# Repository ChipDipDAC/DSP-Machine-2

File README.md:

# DSP-Machine-2
Hi-Res Streamer - Preamp, for Raspberry Pi, XLR analog out<br>
<a class="link" href="https://www.chipdip.ru/catalog-show/for-you-projects?p.0=ChipDipDac"><strong>DSP Machine 2</strong></a> - стример, цифроаналоговый преобразователь ЦАП, аудиопроцессор, для микрокомпьютеров Raspberry Pi.<br />
Для построения стримера вы можете использовать любой микрокомпьютер Raspberry Pi. Микрокомпьютер устанавливается на 40-пиновый разъем аудио карты. В качестве ПО используйте любой плеер или ОС образ, которых записан на микроSD карточку для Raspberry Pi. Операционные системы автоматически определяют аудиокарту ChipDip DAC и настраивают вывод звука именно на неё. В некоторых плеерах может понадобится выбрать в качестве устройства вывода звука - ChipDip DAC.<br />
<br />
- Plug and Play не требует пайки<br />
- Совместим с Raspberry Pi<br />
- Официальная поддержка RaspberryPi OS / Volumio3 / rAudio1 / Album Player / OpenELEC / Manjaro OS / MoOde и другими.<br />
- Высококачественный ЦАП PCM5242 для наилучшего качества звука.<br />
- Разъемы аудиовыхода: 2 x XLR (левый и правый)<br />
- Встроенная EEPROM для автоматической настройки ОС (с защитой от записи).<br />
- Автоматическое переключение частот в соответствии с входными сигналами I2S.<br />
- Диапазон частот дискретизации и разрядности от 44,1кГц/16 бит до 192кГц/32 бит<br />
- Совместим с ПО PurePathStudio и ChipStudio для перестройки аудиопроцессора<br />
Задать вопросы можно на форуме в разделе <a class="link" href="https://forum.chipdip.ru/index.php#chipdip-dac.39">ChipDip DAC</a>
<p></p>

<p></p>

<h2>Что под крышкой *</h2>

<p></p>

<p></p>
* Микрокомпьютер Raspberry Pi в комплект не входит.

<h2>Сравнительная таблица</h2>

<table class="user_t">
	<tbody>
		<tr>
			<td class="tcenter">&nbsp;</td>
			<td class="tcenter">DSP Machine 1</td>
			<td class="tcenter">DSP Machine 2</td>
			<td class="tcenter">DSP Machine 3</td>
		</tr>
		<tr>
			<td class="tcenter">Темброблок</td>
			<td class="tcenter">+</td>
			<td class="tcenter">+</td>
			<td class="tcenter">+</td>
		</tr>
		<tr>
			<td class="tcenter">SuperBass</td>
			<td class="tcenter">+</td>
			<td class="tcenter">+</td>
			<td class="tcenter">+</td>
		</tr>
		<tr>
			<td class="tcenter">Mute</td>
			<td class="tcenter">+</td>
			<td class="tcenter">+</td>
			<td class="tcenter">+</td>
		</tr>
		<tr>
			<td class="tcenter">Блок питания</td>
			<td class="tcenter">+</td>
			<td class="tcenter">+</td>
			<td class="tcenter">+</td>
		</tr>
		<tr>
			<td class="tcenter">Корректное выключение</td>
			<td class="tcenter">+</td>
			<td class="tcenter">+</td>
			<td class="tcenter">+</td>
		</tr>
		<tr>
			<td class="tcenter">Линейный выход</td>
			<td class="tcenter">-</td>
			<td class="tcenter">+</td>
			<td class="tcenter">+</td>
		</tr>
		<tr>
			<td class="tcenter">Усилитель мощности</td>
			<td class="tcenter">+</td>
			<td class="tcenter">-</td>
			<td class="tcenter">-</td>
		</tr>
		<tr>
			<td class="tcenter">Выход SPDIF</td>
			<td class="tcenter">-</td>
			<td class="tcenter">-</td>
			<td class="tcenter">+</td>
		</tr>
		<tr>
			<td class="tcenter">Выход Toslink</td>
			<td class="tcenter">-</td>
			<td class="tcenter">-</td>
			<td class="tcenter">+</td>
		</tr>
		<tr>
			<td class="tcenter">SigmaStudio</td>
			<td class="tcenter">+</td>
			<td class="tcenter">-</td>
			<td class="tcenter">+</td>
		</tr>
		<tr>
			<td class="tcenter">PurePathStudio</td>
			<td class="tcenter">-</td>
			<td class="tcenter">+</td>
			<td class="tcenter">-</td>
		</tr>
		<tr>
			<td class="tcenter">ChipStudio</td>
			<td class="tcenter">+</td>
			<td class="tcenter">+</td>
			<td class="tcenter">+</td>
		</tr>
	</tbody>
</table>
<br />

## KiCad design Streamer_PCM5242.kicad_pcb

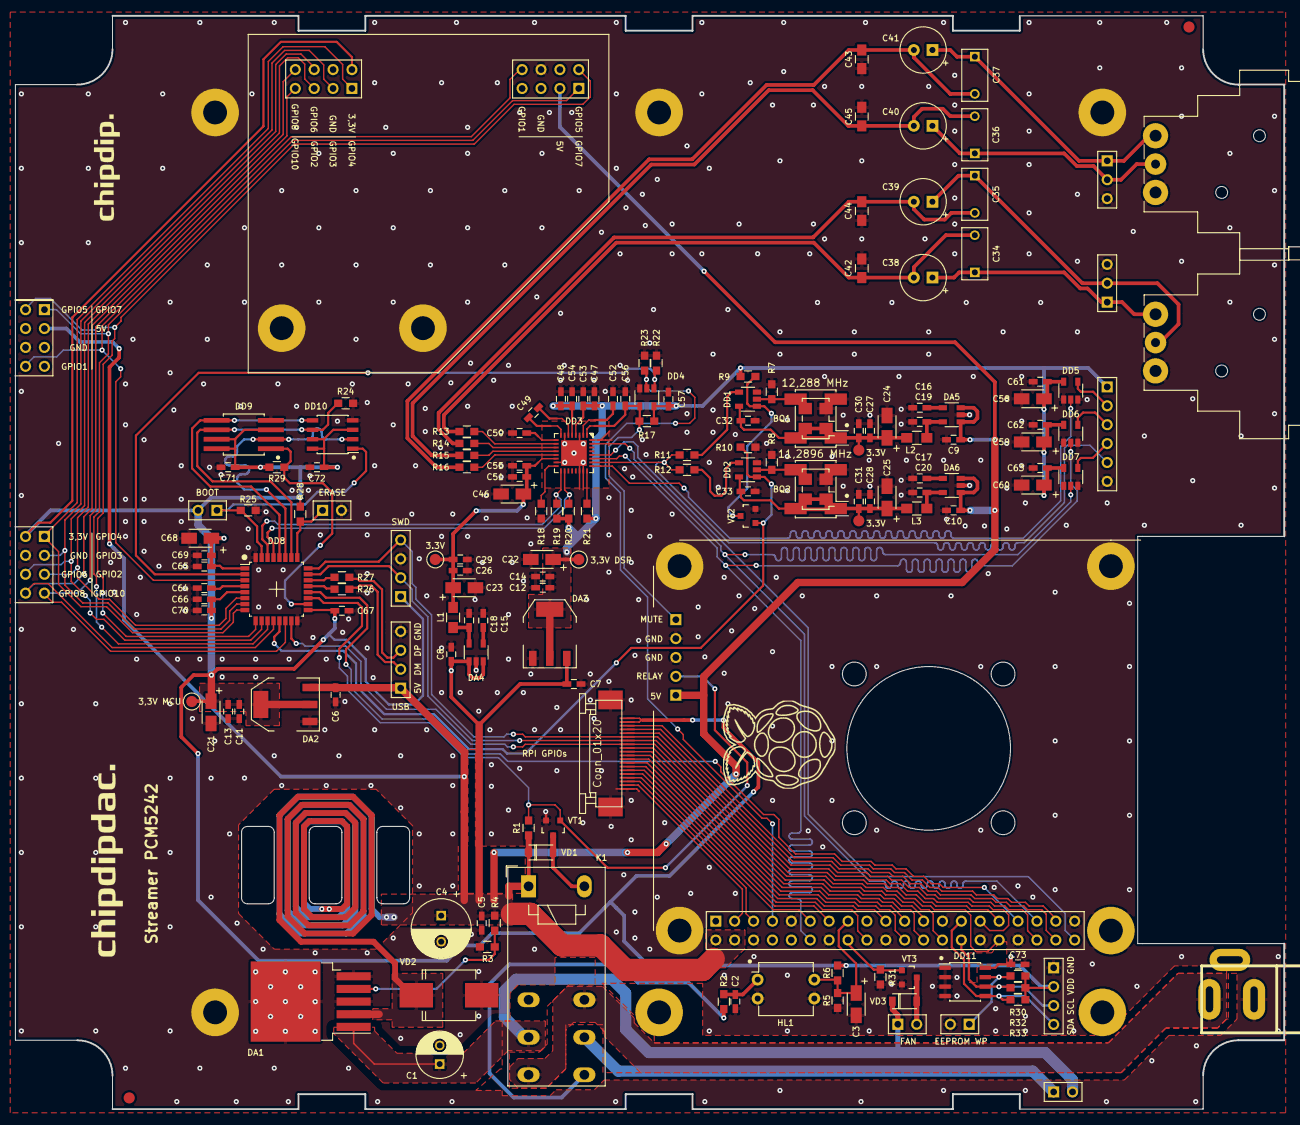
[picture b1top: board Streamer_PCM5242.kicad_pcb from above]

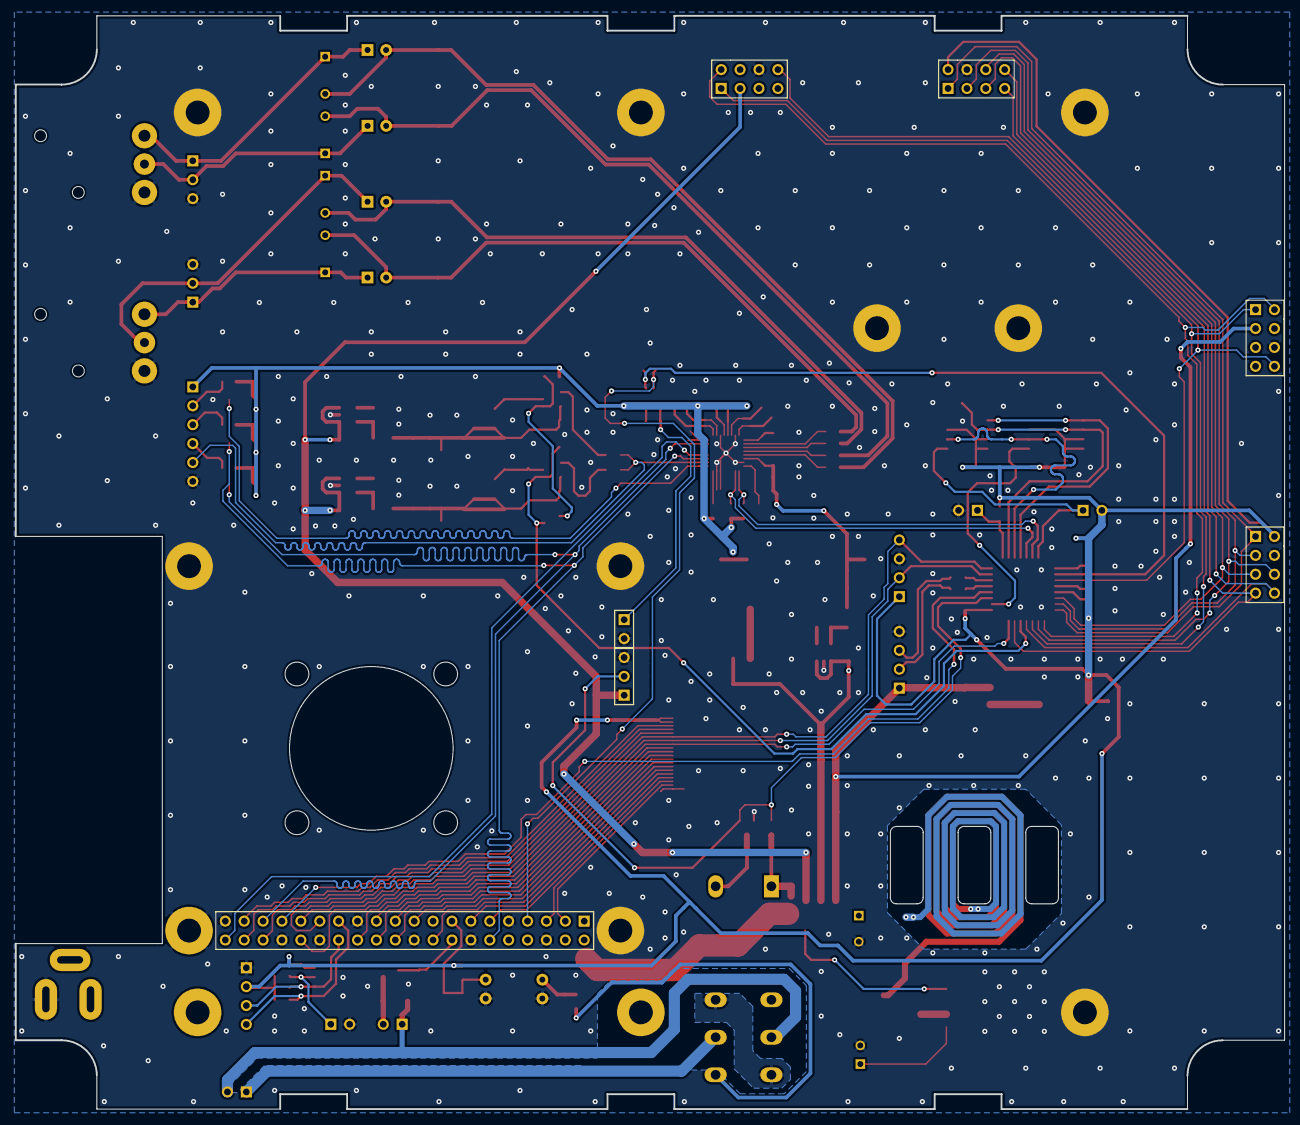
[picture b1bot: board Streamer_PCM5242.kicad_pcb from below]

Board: 2 copper layers, 170.6 x 147.0 mm, 165 parts (7 on the bottom side), 102 nets.

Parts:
BQ1: 12,288MHz; Oscillator_SMD_Fordahl_DFAS2-4Pin_7.3x5.1mm_HandSoldering
BQ2: 11,2896MHz; Oscillator_SMD_Fordahl_DFAS2-4Pin_7.3x5.1mm_HandSoldering
BQ3: 12,288MHz; Oscillator_SMD_EuroQuartz_XO53-4Pin_5.0x3.2mm_HandSoldering
BQ4: 11,2896MHz; Oscillator_SMD_EuroQuartz_XO53-4Pin_5.0x3.2mm_HandSoldering
C1: 100u; C_Radial_D6.3_L11.2_P2.5
C2: 10u; C_0603_HandSoldering
C3, C21, C22, C23, C24, C25, C46, C58, C59, C60, C68: 4.7u; TantalC_SizeA_EIA-3216_mm
C4: 1000u; C_Radial_D8_L11.5_P3.5
C5, C6, C7, C8, C9, C10, C11, C12, C13, C14, C18, C19, C20, C26, C27, C28, C47, C48, C49, C50, C51, C69, C70: 2.2u; C_0603_HandSoldering
C15, C16, C17: 0.01u; C_0603_HandSoldering
C29, C30, C31, C32, C33, C52, C53, C54, C55, C56, C57, C61, C62, C63, C64, C65, C66, C67, C71, C72, C73: 0.1u; C_0603_HandSoldering
C34, C35, C36, C37: 0.47u; C_Rect_L7_W3.5_P5
C38, C39, C40, C41: 10u; CP_Radial_Tantal_D6.0mm_P2.50mm
C42, C43, C44, C45: 2200p; C_0805_HandSoldering
DA1: LM2596S-ADJ; TO-263-5_TabPin3
DA2, DA3: LM1117-3.3; SOT-223
DA4, DA5, DA6: LP2985-3.3; SOT-23-5_mm
DD1, DD2: 74LVC1G125; SOT-23-5_mm
DD3: PCM5242; QFN-32-1EP_5x5mm_P0.5mm_EP3.45x3.45mm
DD4: NC7S08M5X; SOT-23-5_mm
DD5, DD6, DD7: MC74VHC1GT125; SOT-23-5_mm
DD8: STM32F042K6Tx; LQFP-32_7x7mm_Pitch0.8mm
DD9: 25LCxxx; SOIC-8_combo_Pitch1.27mm
DD10: 25LCxxx; SOIC-8_3.9x4.9mm_Pitch1.27mm
DD11: 24LC64; SOIC-8_3.9x4.9mm_Pitch1.27mm
HL1: P814; DIP-4_W7.62mm
K1: RTE2xxxx; Relay_DPDT_Schrack-RT2-FormC_RM5mm
L1, L2, L3: L; R_0805_HandSoldering
P1, P2, P3, P4, P5: Conn_01x01; Measurement_Point_Round-SMD-Pad_Small
R1, R6, R7, R8, R9, R10, R17, R18, R21, R22, R23, R24, R25, R28, R29, R30, R31: 10k; R_0603
R2: 2k; R_0603
R3: 1k; R_0603
R4: 3k; R_0603
R5: 15k; R_0603
R11, R12: 51R; R_0603
R13, R14, R15, R16: 470R; R_0603
R19, R20, R32, R33: 4k7; R_0603
R26, R27: 22; R_0603
VD1, VD3: D; SOD-123
VD2: D_Schottky; DIODE_SMC_Handsoldering
VT1, VT2, VT3: BSS138; SOT-23_mm
XP1, XP4, XP6: Conn_01x03; Pin_Header_Straight_1x03_mm
XP2, XP7, XP9, XP11, XP13, XP14: Conn_01x02; Pin_Header_Straight_1x02_mm
XP3, XP5: XLR3; Jack_XLR_Neutrik_NC3MAAH-1_Horizontal
XP8: Conn_01x06; Pin_Header_Straight_1x06_mm
XP10, XP12, XP15: Conn_01x04; Pin_Header_Straight_1x04_mm
XS1: Conn_01x03; JACK_DC
XS2, XS3, XS4, XS5: Conn_02x04_Odd_Even; Pin_Header_Straight_2x04_mm
XS6: Conn_02x20_Odd_Even; Pin_Header_Straight_2x20_mm
XS7: Conn_01x20; CONN20

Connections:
5V: C4.1, C5.1, C6.1, C7.1, C8.1, C9.1, C10.1, DA1.2, DA2.3, DA3.3, DA4.1, DA4.3, DA5.1, DA5.3, DA6.1, DA6.3, K1.A1, R1.1, R4.1, VD1.1, VD2.1, XP1.1, XP10.1, XS3.3, XS5.3, XS6.2, XS6.4
12V: K1.14, K1.22, XS1.1
BCLK: DD3.27, DD6.2, XS6.12
BCLK_OUT: DD6.4, XP8.3
BOOT\SPI1_NSS3: DD8.31, DD10.1, R25.1, XP9.1
DATA: DD3.28, XS6.40
DATA_OUT: DD5.4, XP8.2
FAN: R31.1, VT3.1, XS6.16
GEN_SEL: DD2.1, DD8.13, R10.1, VT2.1
GND: BQ1.2, BQ2.2, BQ3.2, BQ4.2, C1.2, C2.2, C3.2, C4.2, C5.2, C6.2, C7.2, C8.2, C9.2, C10.2, C11.2, C12.2, C13.2, C14.2, C15.2, C16.2, C17.2, C18.2, C19.2, C20.2, C21.2, C22.2, C23.2, C24.2, C25.2, C26.2, C27.2, C28.2, C29.2, C30.2, C31.2, C32.2, C33.2, C42.1, C43.2, C44.1, C45.2, C46.2, C47.2, C48.2, C50.2, C51.2, C52.2, C53.2, C54.2, C55.2, C56.2, C57.2, C58.2, C59.2, C60.2, C61.2, C62.2, C63.2, C64.2, C65.2, C66.2, C67.2, C68.2, C69.2, C70.2, C71.2, C72.2, C73.2, DA1.3, DA1.5, DA2.1, DA3.1, DA4.2, DA5.2, DA6.2, DD1.3, DD2.3, DD3.3, DD3.7, DD3.15, DD3.22, DD3.23, DD3.32, DD3.33, DD4.3, DD5.1, DD5.3, DD6.1, DD6.3, DD7.1, DD7.3, DD8.16, DD8.32, DD9.4, DD10.4, DD11.1, DD11.2, DD11.3, DD11.4, HL1.2, HL1.3, R3.1, R5.2, R7.1, R8.1, R10.2, R18.2, R22.1, R23.1, R24.1, R25.2, R31.2, VD2.2, VT1.2, VT2.2, VT3.2, XP1.3, XP3.1, XP4.3, XP5.1, XP6.3, XP7.2, XP8.6, XP10.4, XP11.2, XP12.3, XP13.2, XP15.1, XS1.2, XS2.4, XS3.6, XS4.4, XS5.6, XS6.6, XS6.9, XS6.14, XS6.20, XS6.25, XS6.30, XS6.34, XS6.39, XS7.20
GPIO1: DD8.3, XS3.8, XS5.8
GPIO2_BAL: DD8.6, XS2.5, XS4.5
GPIO3_VOL: DD8.7, XS2.3, XS4.3
GPIO4_KEY_1: DD8.8, XS2.1, XS4.1
GPIO5_KEY_2: DD8.9, XS3.2, XS5.2
GPIO6: DD3.25, DD5.2
GPIO6_TREBLE: DD8.10, XS2.6, XS4.6
GPIO7_BASS: DD8.11, XS3.1, XS5.1
GPIO8_LED_COMP: DD8.12, XS2.8, XS4.8
GPIO10_LED_MUTE: DD8.14, XS2.7, XS4.7
I2C1_SCL: DD3.18, DD8.29, R20.1
I2C1_SDA: DD3.17, DD8.30, R19.1
ID_SCL: DD11.6, R32.2, XP15.3, XS6.28
ID_SDA: DD11.5, R33.2, XP15.4, XS6.27
LR: DD3.31, DD7.2, XS6.35
LR_OUT: DD7.4, XP8.4
MUTE: DD4.2, R23.2, XS6.7
MUTE2: DD4.1, DD8.2, R22.2
MUTE_OUT: C56.1, DD3.1, DD4.4, R17.2, XP7.1
unnamed: BQ1.3, BQ3.3, DD1.2, R7.2
unnamed: BQ2.3, BQ4.3, DD2.2, R8.2
unnamed: C2.1, HL1.1, R2.2
unnamed: C15.1, DA4.4
unnamed: C16.1, DA5.4
unnamed: C17.1, DA6.4
unnamed: C18.1, DA4.5, L1.1
unnamed: C19.1, DA5.5, L2.1
unnamed: C20.1, DA6.5, L3.1
unnamed: C34.1, C38.1, XP3.2, XP4.1
unnamed: C34.2, C38.2, C42.2, R13.2
unnamed: C35.1, C39.1, XP3.3, XP4.2
unnamed: C35.2, C39.2, C44.2, R14.2
unnamed: C36.1, C40.1, XP5.3, XP6.2
unnamed: C36.2, C40.2, C45.1, R15.2
unnamed: C37.1, C41.1, XP5.2, XP6.1
unnamed: C37.2, C41.2, C43.1, R16.2
unnamed: C49.1, DD3.6
unnamed: C49.2, DD3.8
unnamed: C50.1, DD3.9
unnamed: C52.1, DD3.2
unnamed: DA1.4, R3.2, R4.2
unnamed: DD1.1, R9.2, VT2.3
unnamed: DD1.4, R11.2
unnamed: DD2.4, R12.2
unnamed: DD3.10, R13.1
unnamed: DD3.11, R14.1
unnamed: DD3.12, R15.1
unnamed: DD3.13, R16.1
unnamed: DD3.16, R18.1
unnamed: DD3.24, R21.2
unnamed: DD8.21, R26.1
unnamed: DD8.22, R27.1
unnamed: DD11.7, R30.2, XP13.1
unnamed: K1.21, XP2.1
unnamed: K1.24, R2.1
unnamed: K1.A2, VD1.2, VT1.3
unnamed: VD3.2, VT3.3, XP14.2
ON_OFF: C3.1, HL1.4, R5.1, R6.2, XS6.15
PWR_EVENT: DD8.20, XS6.33
RAS_GPIO2: XS6.3, XS7.19
RAS_GPIO3: XS6.5, XS7.18
RAS_GPIO7: XS6.26, XS7.9
RAS_GPIO8: XS6.24, XS7.11
RAS_GPIO9: XS6.21, XS7.12
RAS_GPIO10: XS6.19, XS7.14
RAS_GPIO11: XS6.23, XS7.10
RAS_GPIO16: XS6.36, XS7.5
RAS_GPIO17: XS6.11, XS7.17
RAS_GPIO20: XS6.38, XS7.4
RAS_GPIO25: XS6.22, XS7.13
RAS_GPIO26: XS6.37, XS7.3
RELAY: DD8.19, R1.2, VT1.1, XP1.2
RES0: XS6.18, XS7.15
RES1: XS6.13, XS7.16
RST: C64.1, DD8.4
SCK: DD3.26, R11.1, R12.1, XP8.5
SPI1_MISO: DD8.27, DD9.2, DD10.2
SPI1_MOSI: DD8.28, DD9.5, DD10.5
SPI1_NSS1: DD8.25, R28.2, XP11.1
SPI1_NSS2: DD8.18, DD9.1, R29.2
SPI1_SCK: DD8.26, DD9.6, DD10.6, R24.2
SR0: DD8.24, XP12.4, XS6.29, XS7.6
SR1: DD8.23, XP12.2, XS6.31, XS7.7
SR2: DD8.15, XS6.32, XS7.8
USB_DM: R26.2, XP10.2
USB_DP: R27.2, XP10.3
VDD: C11.1, C13.1, C21.1, C65.1, C66.1, C67.1, C68.1, C69.1, C70.1, C71.1, C72.1, C73.1, DA2.2, DA2.4, DD8.1, DD8.5, DD8.17, DD9.3, DD9.7, DD9.8, DD10.3, DD10.7, DD10.8, DD11.8, P1.1, R6.1, R28.1, R29.1, R30.1, R32.1, R33.1, XP9.2, XP12.1, XP15.2, XS2.2, XS4.2, XS7.1, XS7.2
VDDA: C23.1, C26.1, C29.1, C46.1, C51.1, C55.1, DD3.14, L1.2, P3.1
VDD_DSP: C12.1, C14.1, C22.1, C47.1, C48.1, C53.1, C54.1, C57.1, C58.1, C59.1, C60.1, C61.1, C62.1, C63.1, DA3.2, DA3.4, DD3.4, DD3.5, DD4.5, DD5.5, DD6.5, DD7.5, P2.1, R9.1, R17.1, R19.2, R20.2, R21.1, XP8.1
VDD_GEN1: BQ2.1, BQ2.4, BQ4.1, BQ4.4, C25.1, C28.1, C31.1, C33.1, DD2.5, L3.2, P5.1
VDD_GEN2: BQ1.1, BQ1.4, BQ3.1, BQ3.4, C24.1, C27.1, C30.1, C32.1, DD1.5, L2.2, P4.1
VIN: C1.1, DA1.1, K1.11, VD3.1, XP2.2, XP14.1

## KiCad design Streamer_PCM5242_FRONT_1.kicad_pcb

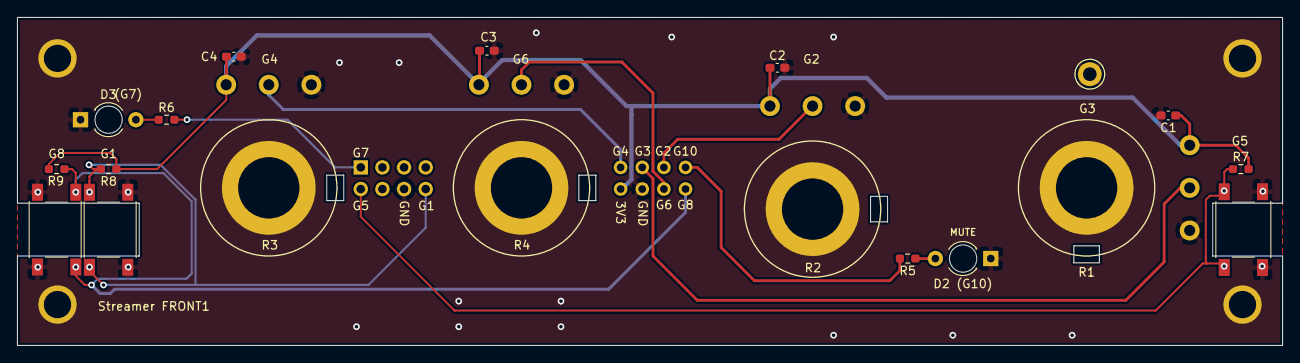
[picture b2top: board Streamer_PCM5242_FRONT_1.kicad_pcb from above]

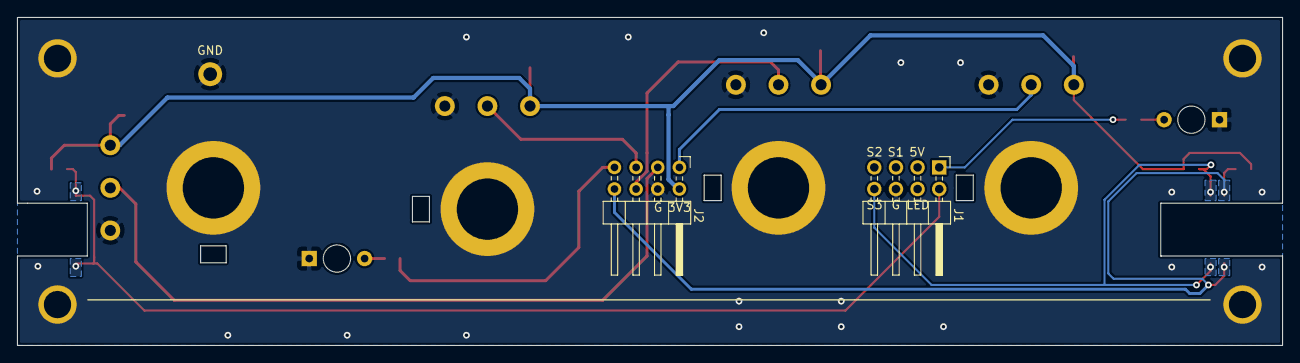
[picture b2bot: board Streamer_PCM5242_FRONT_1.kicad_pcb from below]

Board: 2 copper layers, 148.5 x 38.5 mm, 20 parts (2 on the bottom side), 13 nets.

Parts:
C1, C2, C3, C4: 0.1; C_0603_1608Metric_Pad1.08x0.95mm_HandSolder
D2 (G10), D3: LED; LED_D3.0mm
J1, J2: Conn_02x04_Odd_Even; PinHeader_2x04_P2.54mm_Horizontal
R1, R2, R3, R4: R_POT_TRIM; Potentiometer_Piher_PC-16_Single_Vertical
R5, R6: 560R; R_0603_1608Metric_Pad0.98x0.95mm_HandSolder
R7, R8, R9: 10k; R_0603_1608Metric_Pad0.98x0.95mm_HandSolder
SW1, SW2, SW3: SW_Push_Dual; SW_SPST_PTS645

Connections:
GND: C1.2, C2.2, C3.2, C4.2, D2 (G10).1, D3.1, J1.6, J2.4, R1.3, R2.3, R3.3, R4.3, SW1.1, SW2.1, SW3.1
GPIO1_COMP: J1.8, R8.2, SW2.2
GPIO2_BAL: J2.5, R2.2
GPIO3_VOL: J2.3, R1.2
GPIO4_BASS: J2.1, R3.2
GPIO5_MUTE: J1.2, R7.1, SW1.2
GPIO6_TREBLE: J2.6, R4.2
GPIO7\LED_COMP: J1.1, R6.2
GPIO8_SBASS: J2.8, R9.2, SW3.2
GPIO10\LED_MUTE: J2.7, R5.2
unnamed: D2 (G10).2, R5.1
unnamed: D3.2, R6.1
VDD: C1.1, C2.1, C3.1, C4.1, J2.2, R1.1, R2.1, R3.1, R4.1, R7.2, R8.1, R9.1
